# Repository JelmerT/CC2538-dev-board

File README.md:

CC2538 Development Board
========================

This is the hardware design of a development board for the [CC2538 chip of Texas Instruments](http://www.ti.com/product/cc2538).

You can find more info about the design and hardware decisions [in this blog post](http://jelmertiete.com/2014/05/07/cc2538-development-board/)

The pcb antenna used in this design has its own repository: https://github.com/JelmerT/Eagle-2.4gHz-folded-dipole-pcb-antenna

I also wrote a handy serial bootloader for this dev-board and other CC2538 (and CC26XX and 13XX) hardware, which you can find here: https://github.com/JelmerT/cc2538-bsl

If you improve this design in any way, consider submitting a pull request or contact me. I'd appreciate it if you let me know if you use this design in a real deployment. I'd like to add your project to this page.

License
-------
**This hardware project is released under the [Creative Commons Share-alike 4.0 International](http://creativecommons.org/licenses/by-sa/4.0/) license.**

(C) Jelmer Tiete - <jelmer@tiete.be>

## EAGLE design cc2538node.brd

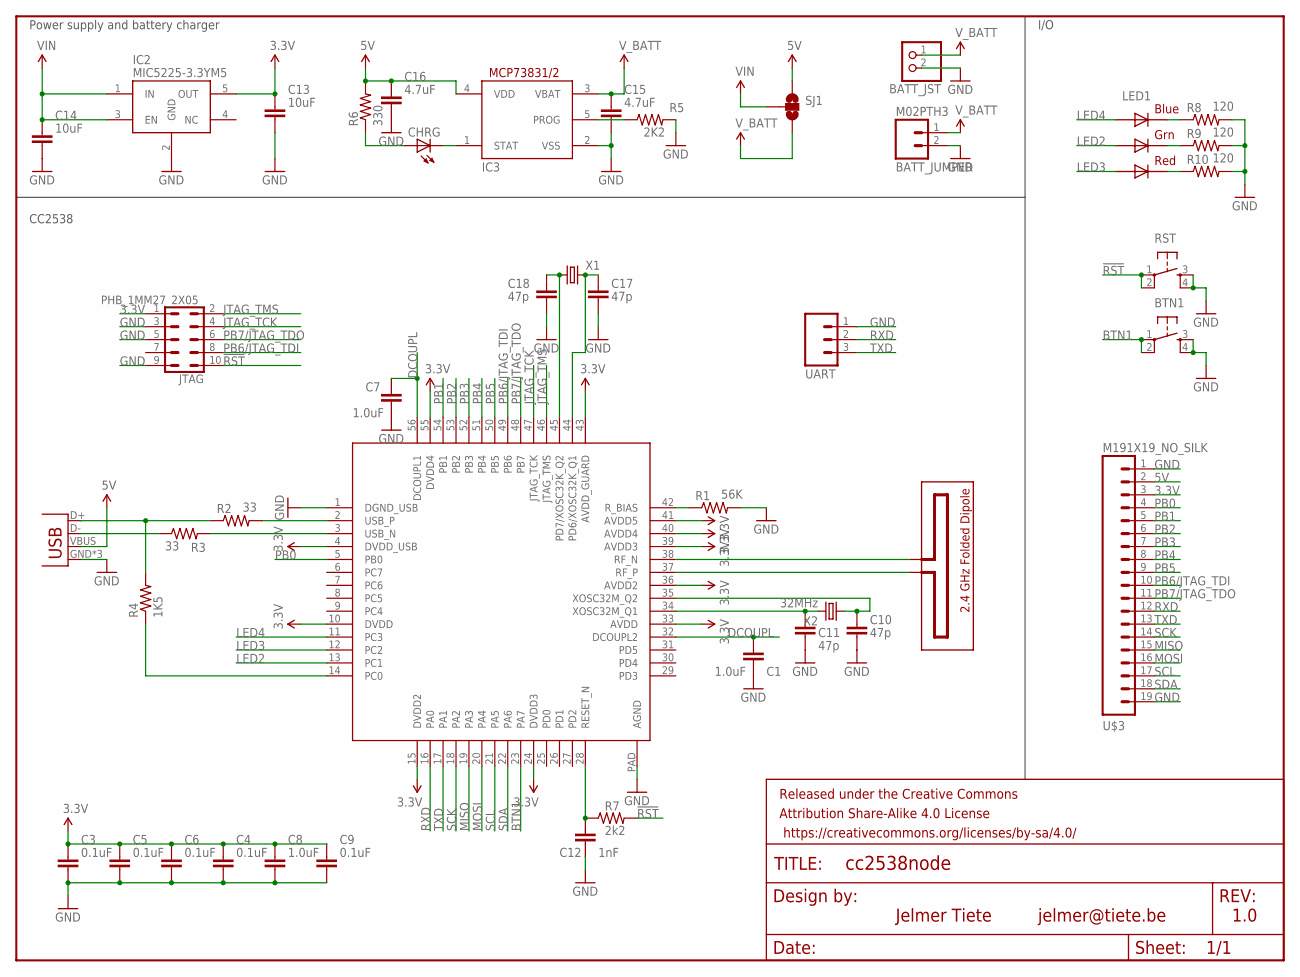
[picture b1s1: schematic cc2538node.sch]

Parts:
BATT_JST: JST_2PIN-SMT-RA; JST-PH-2-SMT-RA
BATT_JUMPER: M02PTH3; 1X02_LONGPADS
BTN1: TAC_SWITCHSMD; TACTILE_SWITCH_SMD
C1, C7, C8: 1.0uF; C603
C3, C4, C5, C6, C9: 0.1uF; C603
C10, C11, C17, C18: 47p; C603
C12: 1nF; C603
C13, C14: 10uF; C603
C15, C16: 4.7uF; C603
CHRG: LED-0603; LED-603
FRAME2: FRAME-LETTER; CREATIVE_COMMONS
IC1: CC2538; QFN56
IC2: MIC5225-3.3YM5; SOT23-5
IC3: MCP73831/OT; SOT23-5L
JP1: USB-MICROB
JTAG: PHB_1MM27_2X05_; PHB_1MM27_2X05_SNT_NOSILK
LED1: RGBLED5050
R1: 56K; 0805
R2, R3: 33; 0805
R4: 1K5; 0805
R5: 2K2; 0805
R6: 330; 0805
R7: 2k2; 0805
R8, R9, R10: 120; 0805
RST: TAC_SWITCHSMD; TACTILE_SWITCH_SMD
SJ1: SOLDERJUMPER_2WAYPASTE1&2; SJ_3_PASTE1&2
U$1: FOLDED_DIPOLE_ANTENNE_2.4; FOLDED_DIPOLE_2.4
U$3: M191X19_NO_SILK; 1X19_NO_SILK
UART: M031X03_NO_SILK; 1X03_NO_SILK
X1: CRYSTAL32-SMD; CRYSTAL-32KHZ-SMD
X2: 32MHz; CTS406

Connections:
3.3V: C3.1, C4.1, C5.1, C6.1, C8.1, C9.1, C13.1, IC1.4 (DVDD_USB), IC1.10 (DVDD), IC1.15 (DVDD2), IC1.24 (DVDD3), IC1.33 (AVDD), IC1.36 (AVDD2), IC1.39 (AVDD3), IC1.40 (AVDD4), IC1.41 (AVDD5), IC1.43 (AVDD_GUARD), IC1.55 (DVDD4), IC2.5 (OUT), JTAG.1, U$3.3
5V: C16.1, IC3.4 (VDD), JP1.VBUS, R6.2, SJ1.1, U$3.2
!RST: JTAG.10, R7.2, RST.1, RST.2
BTN1: BTN1.1, BTN1.2, IC1.23 (PA7)
DCOUPL: C1.1, C7.1, IC1.32 (DCOUPL2), IC1.56 (DCOUPL1)
GND: BATT_JST.2 (1), BATT_JUMPER.2, BTN1.3, BTN1.4, C1.2, C3.2, C4.2, C5.2, C6.2, C7.2, C8.2, C9.2, C10.2, C11.2, C12.2, C13.2, C14.2, C15.2, C16.2, C17.2, C18.2, IC1.1 (DGND_USB), IC1.PAD (AGND), IC2.2 (GND), IC3.2 (VSS), JP1.GND, JP1.MT1 (GND), JP1.MT2 (GND), JTAG.3, JTAG.5, JTAG.9, R1.2, R5.2, R8.2, R9.2, R10.2, RST.3, RST.4, U$3.1, U$3.19, UART.1
JTAG_TCK: IC1.47 (JTAG_TCK), JTAG.4
JTAG_TMS: IC1.46 (JTAG_TMS), JTAG.2
LED2: IC1.13 (PC1), LED1.1 (GREEN_A)
LED3: IC1.12 (PC2), LED1.2 (RED_A)
LED4: IC1.11 (PC3), LED1.3 (BLUE_A)
MISO: IC1.19 (PA3), U$3.15
MOSI: IC1.20 (PA4), U$3.16
unnamed: IC1.38 (RF_N), U$1.P$1
unnamed: IC1.37 (RF_P), U$1.P$2
unnamed: IC1.3 (USB_N), R3.2
unnamed: IC1.2 (USB_P), R2.2
unnamed: LED1.5 (RED_C), R10.1
unnamed: LED1.6 (GREEN_C), R9.1
unnamed: IC1.42 (R_BIAS), R1.1
unnamed: JP1.D+, R2.1, R4.2
unnamed: JP1.D-, R3.1
unnamed: IC1.14 (PC0), R4.1
unnamed: IC3.5 (PROG), R5.1
unnamed: CHRG.C, IC3.1 (STAT)
unnamed: CHRG.A, R6.1
unnamed: C11.1, IC1.34 (XOSC32M_Q1), X2.3 (2)
unnamed: C10.1, IC1.35 (XOSC32M_Q2), X2.1
unnamed: LED1.4 (BLUE_C), R8.1
unnamed: C17.1, IC1.44 (PD6/XOSC32K_Q1), X1.X2 (2)
unnamed: C18.1, IC1.45 (PD7/XOSC32K_Q2), X1.X1 (1)
PB0: IC1.5 (PB0), U$3.4
PB1: IC1.54 (PB1), U$3.5
PB2: IC1.53 (PB2), U$3.6
PB3: IC1.52 (PB3), U$3.7
PB4: IC1.51 (PB4), U$3.8
PB5: IC1.50 (PB5), U$3.9
PB6/JTAG_TDI: IC1.49 (PB6), JTAG.8, U$3.10
PB7/JTAG_TDO: IC1.48 (PB7), JTAG.6, U$3.11
RESET_N: C12.1, IC1.28 (RESET_N), R7.1
RXD: IC1.16 (PA0), U$3.12, UART.2
SCK: IC1.18 (PA2), U$3.14
SCL: IC1.21 (PA5), U$3.17
SDA: IC1.22 (PA6), U$3.18
TXD: IC1.17 (PA1), U$3.13, UART.3
VIN: C14.1, IC2.1 (IN), IC2.3 (EN), SJ1.2
V_BATT: BATT_JST.1 (2), BATT_JUMPER.1, C15.1, IC3.3 (VBAT), SJ1.3

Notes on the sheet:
jelmer@tiete.be
Jelmer Tiete
1.0
Power supply and battery charger
I/O
CC2538

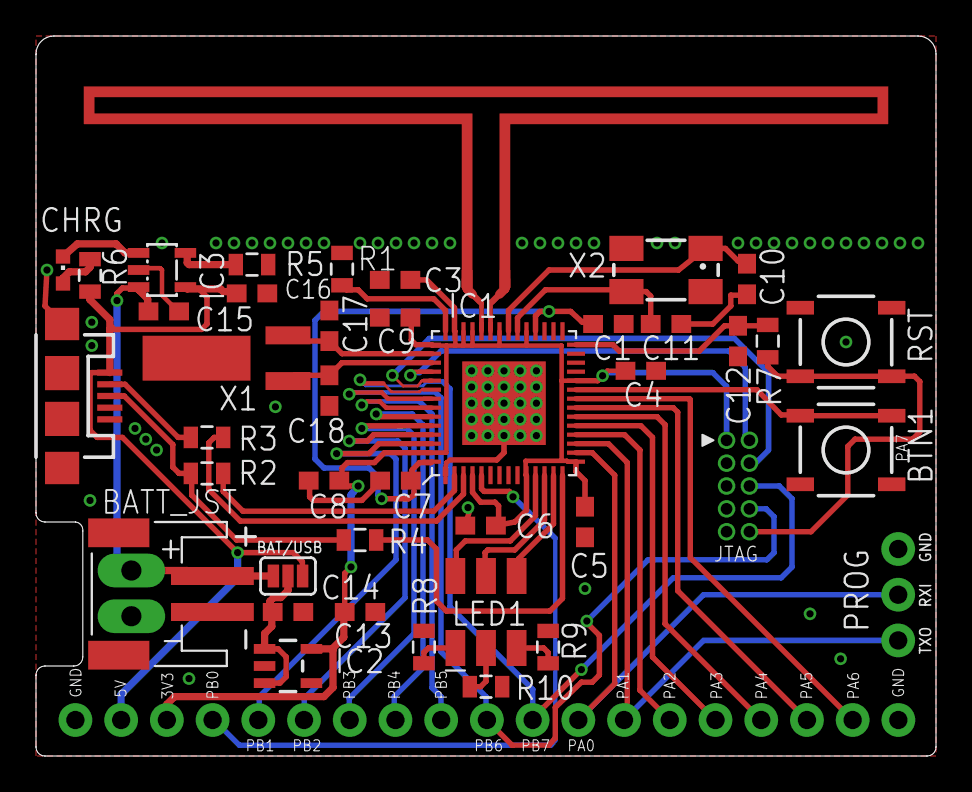
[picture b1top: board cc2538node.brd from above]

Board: 2 copper layers, 50.0 x 40.0 mm, 45 parts (0 on the bottom side), 47 nets.

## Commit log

2015-09-24 First commit, including schematic board file readme and pdfs
2015-09-28 Cleaned up schematic and updated pdfs
2016-01-07 Add gerbers
2016-01-07 Add a 1-click-BOM
2016-05-26 Add kitnic.yaml

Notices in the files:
parts and their libraries:
SparkFun-Connectors: Licensing: CC v3.0 Share-Alike You are welcome to use this library for commercial purposes.
SparkFun-Passives: Licensing: Creative Commons ShareAlike 4.0 International - https://creativecommons.org/licenses/by-sa/4.0
